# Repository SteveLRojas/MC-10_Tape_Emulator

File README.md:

# MC-10_Tape_Emulator
Unified HW and SW repository for the TRS-80 MC-10 tape emulator project.

## Dev Plan (USB Lib/FATFS)
✅- Get the STM to compile, 
- investigate funcs on top of in/out/transact to see how to use them to accomplish various operations
- Try to enumerate?
- Build bulk-only stuff?
- Implement SCSI stuff using bulk-only?
- ...??
- Glue functions?

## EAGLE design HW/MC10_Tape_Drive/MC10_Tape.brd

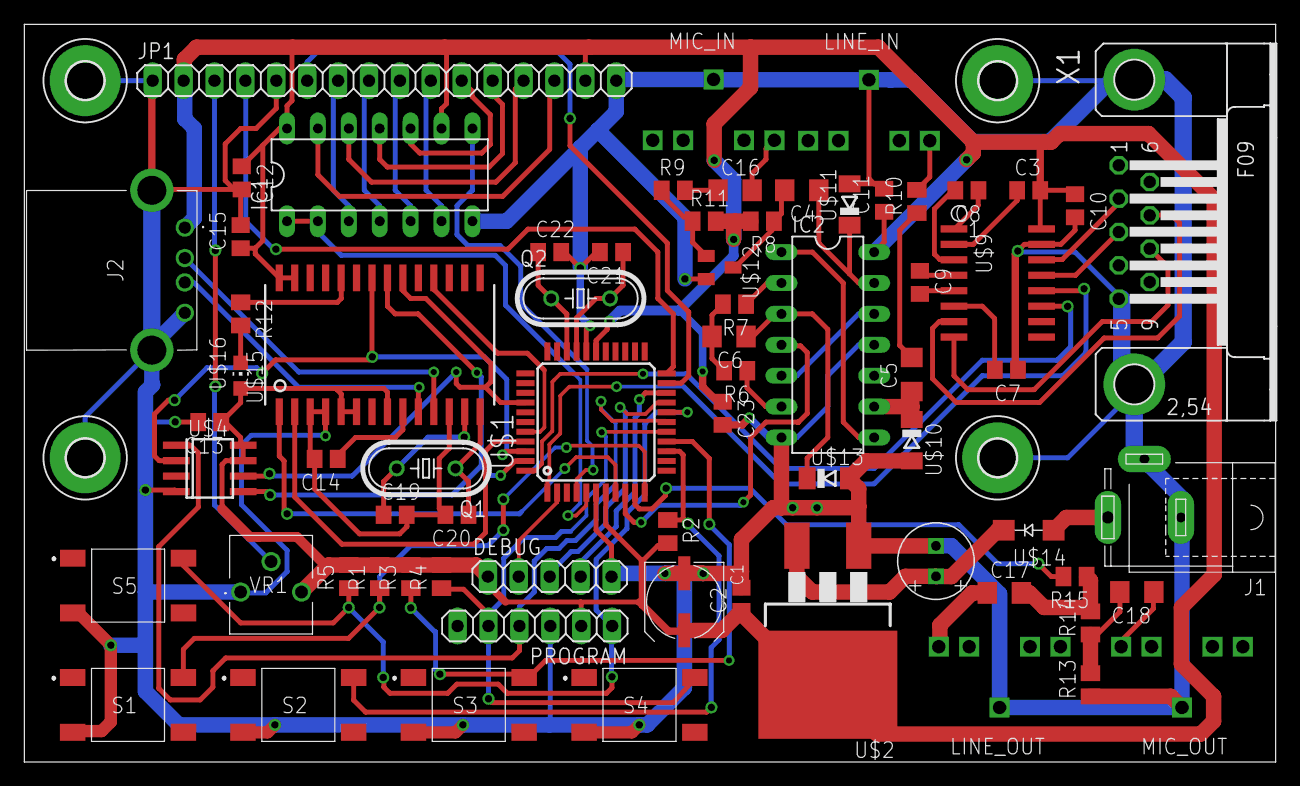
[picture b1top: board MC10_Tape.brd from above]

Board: 2 copper layers, 102.8 x 60.6 mm, 74 parts (0 on the bottom side), 73 nets.

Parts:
C1: UD-6,3X5,8_NICHICON
C2, C3, C7, C8, C9, C10, C11, C12, C13, C14, C15, C23: 104; C0805
C4, C5, C6, C16, C17, C18: 106; C1206
C19, C20, C21, C22: 22p; C0805
DEBUG: 1X05
H1, H2, H3, H4: MOUNT-PAD-ROUND3.0; 3,0-PAD
IC1: 74164N; DIL14
IC2: 7414N; DIL14
J1: SPC4077
J2: 87520-0010BLF; 875200010BLF
JP1: 1X16
LINE_IN: 3.5_AUDIO
LINE_OUT: 3.5_AUDIO
MIC_IN: 3.5_AUDIO
MIC_OUT: 3.5_AUDIO
PROGRAM: 1X06
Q1, Q2: HC49/S
R1, R2, R3, R4, R5, R6, R7, R13: 1k; M0805
R8, R9, R10, R12: 470; M0805
R11: 120k; M0805
R14: 4k7; M0805
R15: 10k; M0805
S1, S2, S3, S4, S5: LL3301NF065QG
U$1: PIC16F747-IPT; TQFP44
U$2: LM1086; D2PACK
U$3: NXA_35V100_6.3X11
U$4: 23LC512T-ISN; SO08
U$9: SP232; SOP16
U$10, U$11, U$13: ZMM2V2; SOD80C
U$12: PMBT3904; SOT23
U$14: SS24; SMA-DO214AC
U$15: CH376S; SOP28
U$16: LED_0805; CHIP-LED0805
VR1: 3306P-1-473; 3306P1104
X1: F09HP

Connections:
5V0: C1.+, C2.1, C3.2, C10.1, C11.1, C12.1, C13.1, C15.1, C23.1, DEBUG.1, IC1.9, IC1.14, IC2.14, J2.1, JP1.2, JP1.15, PROGRAM.2, R1.2, R2.2, R3.2, R4.2, R5.2, R8.2, R11.2, U$1.7, U$1.28, U$2.2, U$4.7, U$4.8, U$9.16, U$15.5, U$15.6, U$15.8, U$15.27, U$15.28, U$16.A, VR1.3
D0: IC1.3, JP1.7
D1: IC1.4, JP1.8
D2: IC1.5, JP1.9
D3: IC1.6, JP1.10
D4: IC1.10, JP1.11
D5: IC1.11, JP1.12
D6: IC1.12, JP1.13
D7: IC1.13, JP1.14
DEBUG: DEBUG.2, U$1.2
DISP_CLK: IC1.8, U$1.4
DISP_DATA: IC1.1, IC1.2, U$1.5
E: JP1.6, U$1.21
GND: C1.-, C2.2, C7.1, C10.2, C11.2, C12.2, C13.2, C14.2, C15.2, C19.2, C20.2, C21.2, C22.2, C23.2, DEBUG.5, H1.B3,0, H2.B3,0, H3.B3,0, H4.B3,0, IC1.7, IC2.7, IC2.11, J1.1, J1.2, J2.4, J2.MH1, J2.MH2, JP1.1, JP1.5, JP1.16, LINE_IN.SLEEVE, LINE_OUT.SLEEVE, MIC_IN.SLEEVE, MIC_OUT.SLEEVE, PROGRAM.3, R13.1, S1.3, S2.3, S3.3, S4.3, S5.3, U$1.6, U$1.29, U$2.1, U$3.P$1, U$4.4, U$9.15, U$10.A, U$11.A, U$12.2, U$13.A, U$15.3, U$15.4, U$15.12, VR1.1, X1.5, X1.G1, X1.G2
LINE_IN: LINE_IN.RING, R10.2
LINE_OUT: C17.1, LINE_OUT.RING
MIC_IN: C16.2, MIC_IN.RING
MIC_OUT: C18.1, MIC_OUT.RING
MISO: U$1.42, U$4.2, U$15.22
MOSI: U$1.43, U$4.5, U$15.21
unnamed: C5.1, IC2.9, U$10.C
unnamed: U$2.3, U$3.P$2, U$14.K
unnamed: C6.1, IC2.3, U$13.C
unnamed: IC2.1, IC2.8
unnamed: IC2.5, IC2.12
unnamed: C14.1, U$15.9
unnamed: C4.2, R8.1, U$12.3
unnamed: C4.1, IC2.13, U$11.C
unnamed: R9.1, R11.1, U$12.1
unnamed: C17.2, R14.2, R15.1
unnamed: R12.2, U$16.C
unnamed: C16.1, R9.2
unnamed: IC2.6, R6.1
unnamed: C6.2, R6.2, R7.2
unnamed: IC2.2, R7.1
unnamed: C18.2, R13.2, R14.1
unnamed: C21.1, Q2.2, U$1.30
unnamed: C20.1, Q1.1, U$15.14
unnamed: C19.1, Q1.2, U$15.13
unnamed: C22.1, Q2.1, U$1.31
unnamed: R12.1, U$15.24
unnamed: J1.3, U$14.A
unnamed: C8.2, U$9.3
unnamed: C8.1, U$9.1
unnamed: C9.2, U$9.5
unnamed: C9.1, U$9.4
unnamed: C3.1, U$9.2
unnamed: C7.2, U$9.6
unnamed: C5.2, R10.1
RS: JP1.4, U$1.22
RS232_CTS: U$9.7, X1.7
RS232_RTS: U$9.8, X1.8
RS232_RXD: U$9.13, X1.3
RS232_TXD: U$9.14, X1.2
RXD: U$1.1, U$9.12
SCK: U$1.37, U$4.6, U$15.20
SW0: R1.1, S1.2, U$1.11
SW1: R2.1, S2.2, U$1.14
SW2: R3.1, S3.2, U$1.15
SW3: PROGRAM.5, R4.1, S4.2, U$1.16
S_RX: DEBUG.4, U$1.20
S_TX: DEBUG.3, U$1.19
TAPE_IN: IC2.4, U$1.9
TAPE_OUT: R15.2, U$1.10
TXD: U$1.44, U$9.11
USB_CS: U$1.40, U$15.18
USB_D+: J2.3, U$15.10
USB_D-: J2.2, U$15.11
USB_INT: U$1.8, U$15.1
USB_RST: U$1.41, U$15.2
V0: JP1.3, VR1.2
~RAM_CS: PROGRAM.4, U$1.17, U$4.1
~RESET: PROGRAM.1, R5.1, S5.2, U$1.18

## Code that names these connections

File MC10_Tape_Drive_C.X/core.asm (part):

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    
#define DISP_E PORTA, 2
#define DISP_RS PORTA, 3
#define USB_INT PORTB, 0
#define TAPE_IN PORTB, 1
#define TAPE_OUT PORTB, 2
#define SW0 PORTB, 3
#define SW1 PORTB, 4
#define SW2 PORTB, 5
#define SW3 PORTB, 6
#define RAM_CS PORTB, 7
#define USB_CS PORTD, 2
#define USB_RST PORTD, 3
#define DISP_CLK PORTD, 6
#define DISP_DATA PORTD, 7
    
#define F_SRL_VALID _flag_reg, 0
#define F_BB_FIRST _flag_reg, 1
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
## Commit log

2023-05-27 Added files
2023-05-28 Enabled usb file read
2023-05-29 Fixed many bugs
2023-05-29 Write test data
2023-06-10 Write file
2023-10-27 Cleaned up project structure, added new HW
2023-11-26 Created MRS project
2023-12-19 Did some stuff
2024-01-12 removed backups
2024-01-13 added CDC test project
2024-01-13 Added BOM
2024-01-14 Created CDC FIFO in test project
2024-01-14 Cleaned up CDC test project
2024-01-21 CDC now using fifo buffers, cleanup pending
2024-01-25 implemented fifo to pma copy function
2024-01-27 Implemented PMA to receive buffer copy function
2024-01-27 Cleaned up code
2024-01-27 cleanup stuff
2024-02-10 Created CDC interface files
2024-02-10 removed/replaced stuff from UART.c UART.h
2024-02-10 Completed CDC serial, needs checking/cleanup
2024-02-18 Completed CDC test project
2024-03-07 Added USB mass storage test projects
2024-03-12 WIP implementing SCSI and BOT
2024-03-17 Got SCSI TestUnitReady partially working
2024-03-27 Using LED and buttons, SCSI TestUnitReady working for most flash drives
2024-03-31 Got SCSI Inquiry working, improved enumeration
2024-04-01 Got SCSI ReadCapacity working
2024-05-04 Get endpoint number from endpoint descriptor
2024-05-08 Got SCSI read working
2024-05-25 FatFs glue functions, got file read working
2024-05-26 Got file write working
2024-09-04 Created a new MRS project without WCH libraries
2024-09-07 Enumerate and configure flash drive using new libraries
2025-04-16 mystery changes I forgot to commit...
